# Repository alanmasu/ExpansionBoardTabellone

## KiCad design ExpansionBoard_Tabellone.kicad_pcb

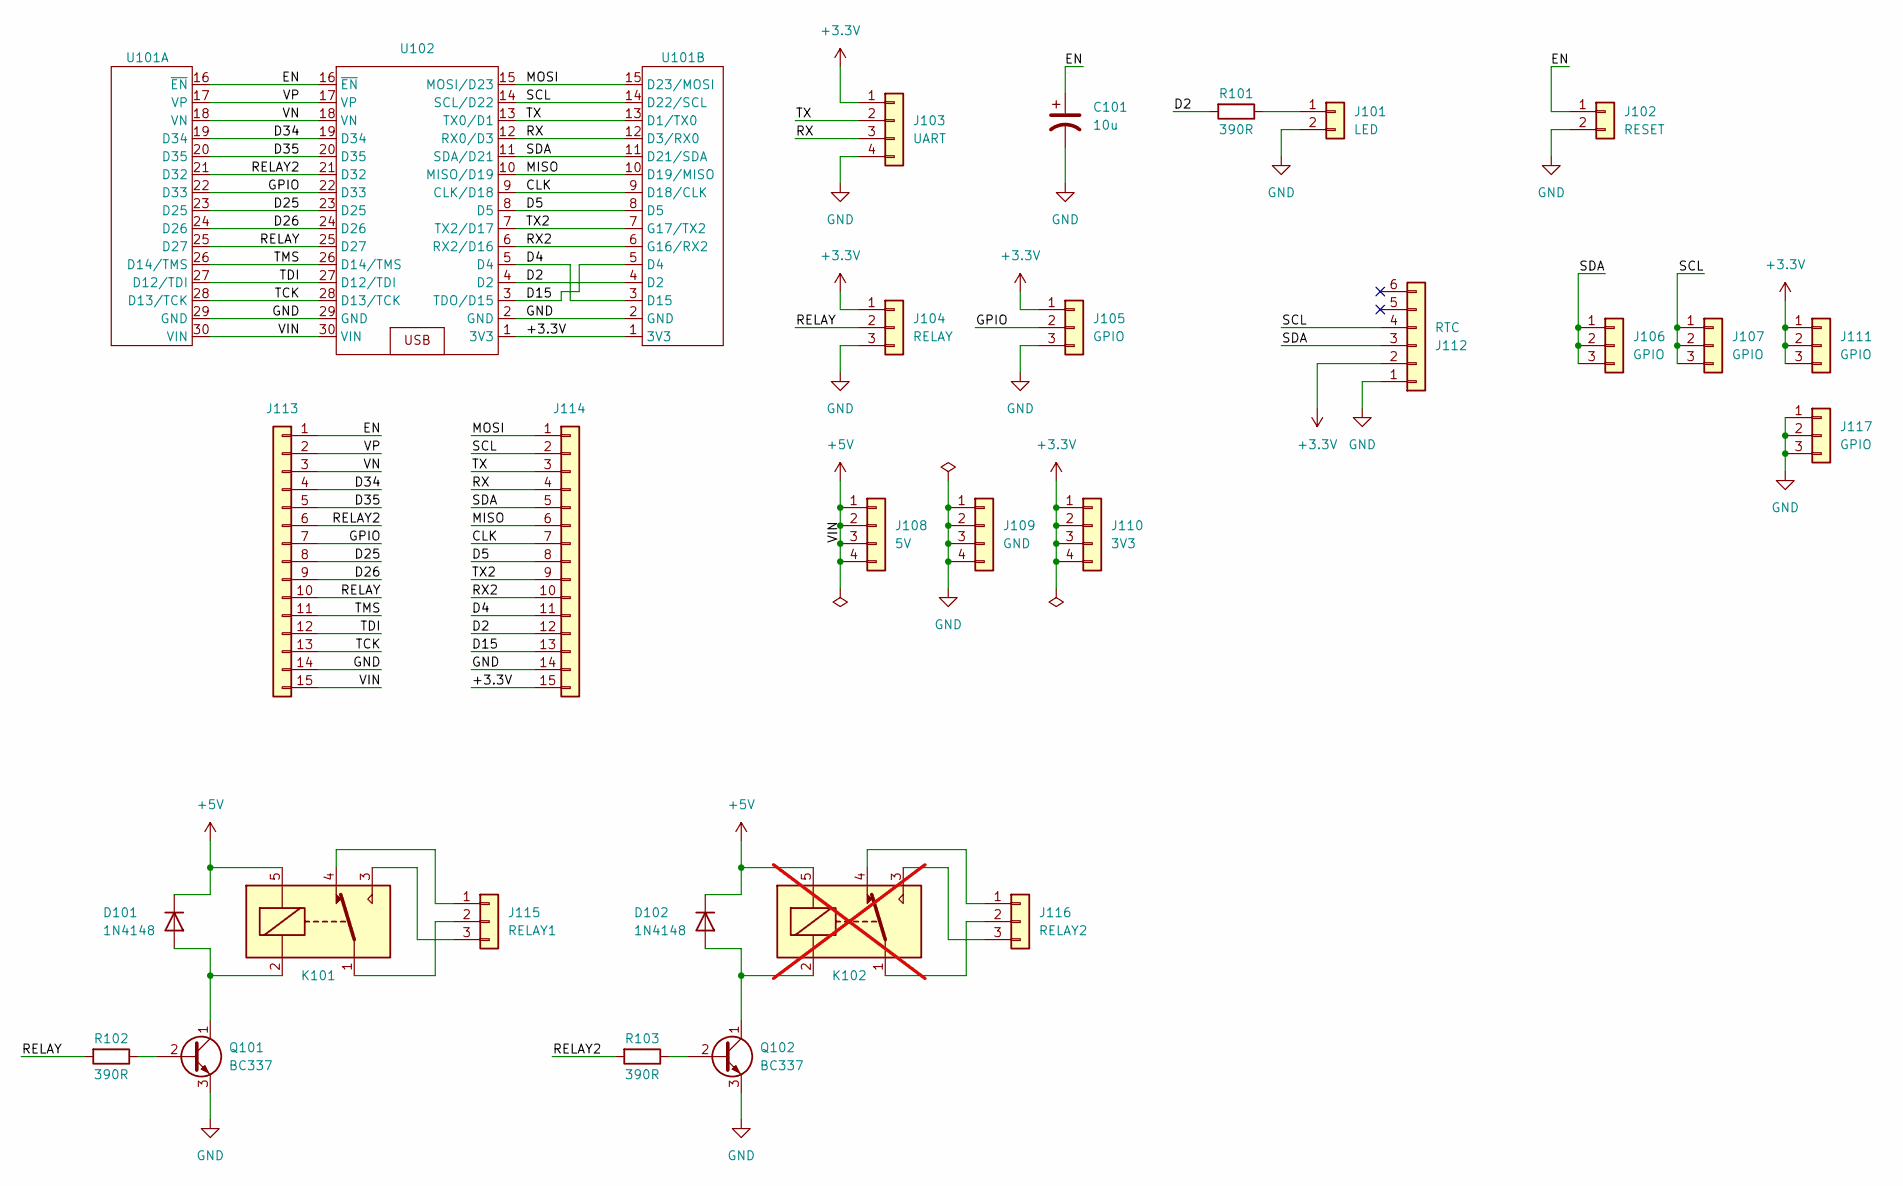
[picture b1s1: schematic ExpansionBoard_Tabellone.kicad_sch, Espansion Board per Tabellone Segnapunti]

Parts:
C101: 10u; CP_Radial_D5.0mm_P2.00mm
D101, D102: 1N4148; D_DO-35_SOD27_P7.62mm_Horizontal
J101: LED; PinSocket_1x02_P2.54mm_Vertical_HandSoldering
J102: RESET; PinSocket_1x02_P2.54mm_Vertical_HandSoldering
J103: UART; PinSocket_1x04_P2.54mm_Vertical_HandSoldering
J104: RELAY; PinSocket_1x03_P2.54mm_Vertical_HandSoldering
J105, J106, J107, J111, J117: GPIO; PinSocket_1x03_P2.54mm_Vertical_HandSoldering
J108: 5V; PinSocket_1x04_P2.54mm_Vertical_HandSoldering
J109: GND; PinSocket_1x04_P2.54mm_Vertical_HandSoldering
J110: 3V3; PinSocket_1x04_P2.54mm_Vertical_HandSoldering
J112: RTC; PinSocket_1x06_P2.54mm_Vertical_HandSoldering
J113, J114: Conn_01x15; PinSocket_1x15_P2.54mm_Vertical_HandSoldering
J115: RELAY1; ScrewConnector_1x03_P5.08mm_HandSoldering
J116: RELAY2; PinSocket_1x03_P2.54mm_Vertical_HandSoldering
K101: SANYOU_SRD_Form_C; Relay_SPDT_SANYOU_SRD_Series_Form_C
K102: SANYOU_SRD_Form_C; Relay_SPDT_SANYOU_SRD_Series_Form_C; not fitted
Q101, Q102: BC337; TO-92_HandSolder
R101, R102, R103: 390R; R_Axial_DIN0207_L6.3mm_D2.5mm_P10.16mm_Horizontal
U101: TabelloneBoard_HandSoldering
U102: ESP_WROOM_32_DevKit_HandSoldering

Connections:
+3.3V: J103.1, J104.1, J105.1, J110.1, J110.2, J110.3, J110.4, J111.1, J111.2, J111.3, J112.2, J114.15, U101.1 (3V3), U102.1 (3V3)
+5V: D101.1 (K), D102.1 (K), J108.1, J108.2, J108.3, J108.4, J113.15, K101.5, K102.5, U101.30 (VIN), U102.30 (VIN)
/CLK: J114.7, U101.9 (D18/CLK), U102.9 (CLK/D18)
/D2: J114.12, R101.2, U101.4 (D2), U102.4 (D2)
/D4: J114.11, U101.3 (D15), U102.5 (D4)
/D5: J114.8, U101.8 (D5), U102.8 (D5)
/D15: J114.13, U101.5 (D4), U102.3 (TDO/D15)
/D25: J113.8, U101.23 (D25), U102.23 (D25)
/D26: J113.9, U101.24 (D26), U102.24 (D26)
/D34: J113.4, U101.19 (D34), U102.19 (D34)
/D35: J113.5, U101.20 (D35), U102.20 (D35)
/EN: C101.1, J102.1, J113.1, U101.16 (~EN), U102.16 (~EN)
/GPIO: J105.2, J113.7, U101.22 (D33), U102.22 (D33)
/MISO: J114.6, U101.10 (D19/MISO), U102.10 (MISO/D19)
/MOSI: J114.1, U101.15 (D23/MOSI), U102.15 (MOSI/D23)
/RELAY: J104.2, J113.10, R102.2, U101.25 (D27), U102.25 (D27)
/RELAY2: J113.6, R103.2, U101.21 (D32), U102.21 (D32)
/RX: J103.3, J114.4, U101.12 (D3/RX0), U102.12 (RX0/D3)
/RX2: J114.10, U101.6 (G16/RX2), U102.6 (RX2/D16)
/SCL: J107.1, J107.2, J107.3, J112.4, J114.2, U101.14 (D22/SCL), U102.14 (SCL/D22)
/SDA: J106.1, J106.2, J106.3, J112.3, J114.5, U101.11 (D21/SDA), U102.11 (SDA/D21)
/TCK: J113.13, U101.28 (D13/TCK), U102.28 (D13/TCK)
/TDI: J113.12, U101.27 (D12/TDI), U102.27 (D12/TDI)
/TMS: J113.11, U101.26 (D14/TMS), U102.26 (D14/TMS)
/TX: J103.2, J114.3, U101.13 (D1/TX0), U102.13 (TX0/D1)
/TX2: J114.9, U101.7 (G17/TX2), U102.7 (TX2/D17)
/VN: J113.3, U101.18 (VN), U102.18 (VN)
/VP: J113.2, U101.17 (VP), U102.17 (VP)
GND: C101.2, J101.2, J102.2, J103.4, J104.3, J105.3, J109.1, J109.2, J109.3, J109.4, J112.1, J113.14, J114.14, J117.1, J117.2, J117.3, Q101.3 (E), Q102.3 (E), U101.2 (GND), U101.29 (GND), U102.2 (GND), U102.29 (GND)
unnamed: D101.2 (A), K101.2, Q101.1 (C)
unnamed: D102.2 (A), K102.2, Q102.1 (C)
unnamed: J101.1, R101.1
unnamed: J115.1, K101.4
unnamed: J115.2, K101.1
unnamed: J115.3, K101.3
unnamed: J116.1, K102.4
unnamed: J116.2, K102.1
unnamed: J116.3, K102.3
unnamed: Q101.2 (B), R102.1
unnamed: Q102.2 (B), R103.1

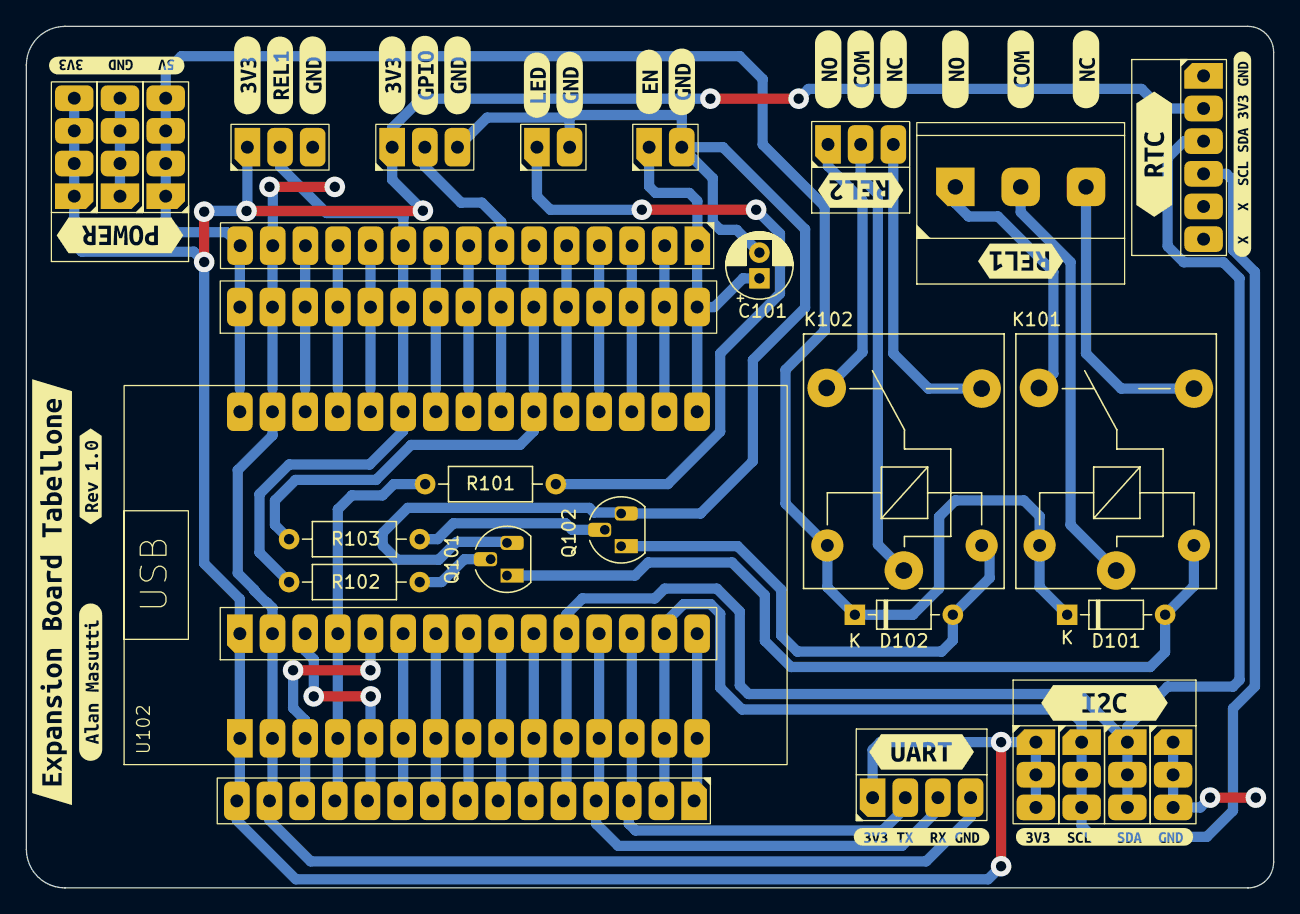
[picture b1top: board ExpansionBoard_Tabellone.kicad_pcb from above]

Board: 2 copper layers, 97.0 x 67.0 mm, 58 parts (0 on the bottom side), 40 nets.

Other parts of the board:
kibuzzard-674D9E9C: G***; kibuzzard-674D9E9C
kibuzzard-674D90DD: G***; kibuzzard-674D90DD
kibuzzard-674D92E6: G***; kibuzzard-674D92E6
kibuzzard-674D96AF: G***; kibuzzard-674D96AF
kibuzzard-674D96D9: G***; kibuzzard-674D96D9
kibuzzard-674D900C: G***; kibuzzard-674D900C
kibuzzard-674D949E: G***; kibuzzard-674D949E
kibuzzard-674D952B, kibuzzard-674D952B#2: G***; kibuzzard-674D952B
kibuzzard-674D955A: G***; kibuzzard-674D955A
kibuzzard-674D958A: G***; kibuzzard-674D958A
kibuzzard-674D960A, kibuzzard-674D960A#2: G***; kibuzzard-674D960A
kibuzzard-674D9199: G***; kibuzzard-674D9199
kibuzzard-674D9352: G***; kibuzzard-674D9352
kibuzzard-674D9524: G***; kibuzzard-674D9524
kibuzzard-674D9540, kibuzzard-674D9540#2: G***; kibuzzard-674D9540
kibuzzard-674D9590: G***; kibuzzard-674D9590
kibuzzard-674D9611, kibuzzard-674D9611#2: G***; kibuzzard-674D9611
kibuzzard-674D9616, kibuzzard-674D9616#2: G***; kibuzzard-674D9616
kibuzzard-674DA1B7: G***; kibuzzard-674DA1B7
kibuzzard-674DC36A: G***; kibuzzard-674DC36A
kibuzzard-674DC425: G***; kibuzzard-674DC425
kibuzzard-674DD7AD: G***; kibuzzard-674DD7AD
kibuzzard-674DD7E6: G***; kibuzzard-674DD7E6
kibuzzard-674DD811: G***; kibuzzard-674DD811

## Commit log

2024-11-30 Disegnato lo schematico
2024-11-30 Modificato footprint TabelloneBoard
2024-11-30 Spostate le label lato Pin ESP e non lato board
2024-11-30 Cambiate le impronte ai connettori
2024-12-02 Cambiato un footprint
2024-12-02 Aggiunti i Relè nello schematico
2024-12-02 Modificato connettore RTC
2024-12-02 Copletato anche il routing
    Cambiato anche il morsetto del Rele1
2024-12-05 Ultime modifiche
    - Inserito connettore per relè
    - Compilati i cartigli
    - Ultimi fix
2024-12-05 Aggiunta la licenza
